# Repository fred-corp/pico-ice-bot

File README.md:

# Pico ICE Bot

A simple robot chassis bot for the Pico-ICE FPGA dev board.

## License & Acknowledgements

Made with ❤️, lots of ☕️, and lack of 🛌  
Published under CreativeCommons BY-SA 4.0

This work is licensed under a [Creative Commons Attribution-ShareAlike 4.0 International License](http://creativecommons.org/licenses/by-sa/4.0/).

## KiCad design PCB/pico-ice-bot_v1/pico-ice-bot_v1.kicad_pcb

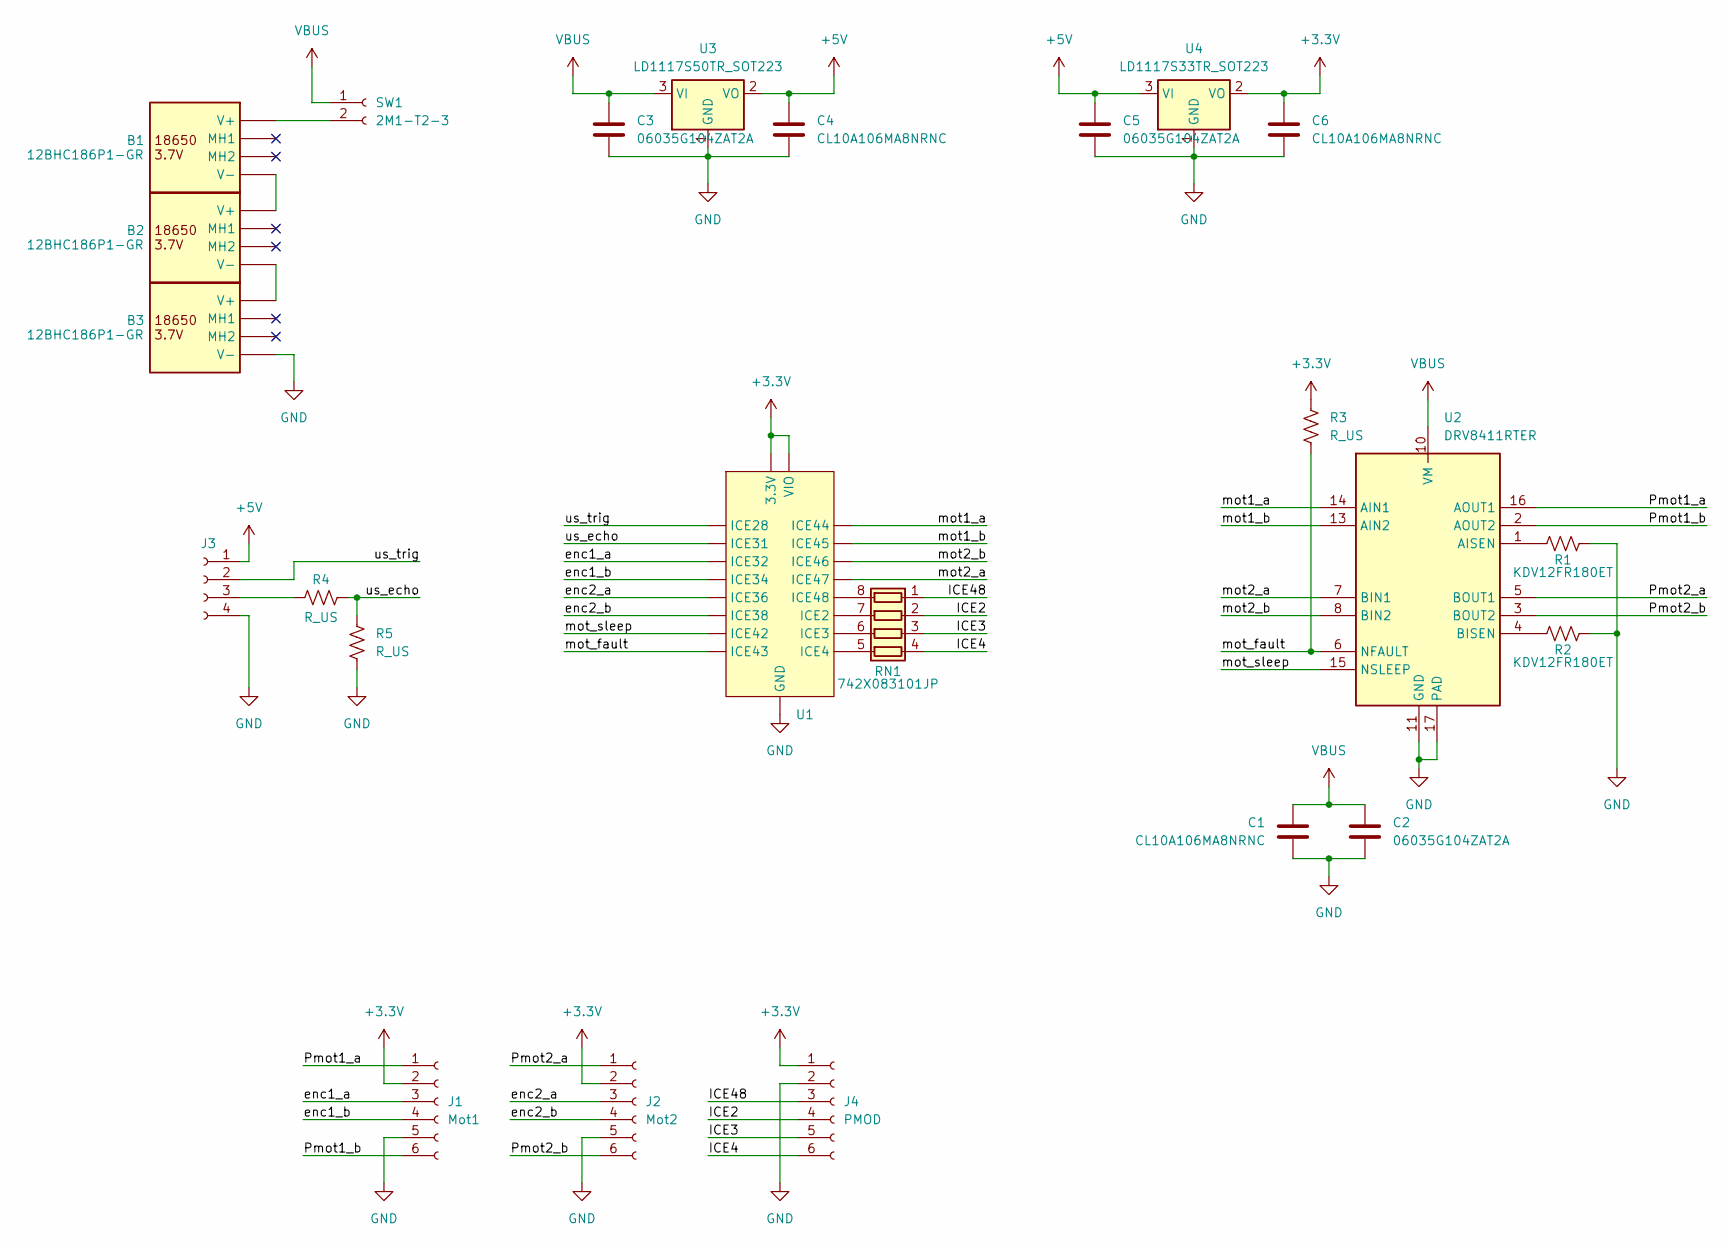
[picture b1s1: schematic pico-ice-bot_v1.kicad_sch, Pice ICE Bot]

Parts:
B1, B2, B3: 12BHC186P1-GR; 12BHC186P1GR; Mouser Part Number 12BHC186P1-GR
C1, C4, C6: CL10A106MA8NRNC; C_0603_1608Metric_Pad1.08x0.95mm_HandSolder
C2, C3, C5: 06035G104ZAT2A; C_0603_1608Metric_Pad1.08x0.95mm_HandSolder
J1: Mot1; PinSocket_1x06_P2.54mm_Vertical
J2: Mot2; PinSocket_1x06_P2.54mm_Vertical
J3: Conn_01x04_Socket; PinHeader_1x04_P2.54mm_Vertical
J4: PMOD; PinSocket_1x06_P2.54mm_Vertical
R1, R2: KDV12FR180ET; R_1206_3216Metric_Pad1.30x1.75mm_HandSolder
R3, R4, R5: R_US; R_0603_1608Metric_Pad0.98x0.95mm_HandSolder
RN1: 742X083101JP; R_Array_Concave_4x0603
SW1: 2M1-T2-3; PinHeader_1x02_P2.54mm_Vertical
U1: pico-ice-pmod_vertical
U2: DRV8411RTER; QFN50P300X300X80-17N-D; Mouser Part Number 595-DRV8411RTER
U3: LD1117S50TR_SOT223; SOT-223-3_TabPin2
U4: LD1117S33TR_SOT223; SOT-223-3_TabPin2

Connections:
+3.3V: C6.1, J1.2, J2.2, J4.1, R3.1, U1.1 (3.3V), U1.2 (3.3V), U1.13 (VIO), U1.14 (VIO), U4.2 (VO)
+5V: C4.1, C5.1, J3.1, U3.2 (VO), U4.3 (VI)
/ICE2: J4.4, RN1.2 (R2.1)
/ICE3: J4.5, RN1.3 (R3.1)
/ICE4: J4.6, RN1.4 (R4.1)
/ICE48: J4.3, RN1.1 (R1.1)
/Pmot1_a: J1.1, U2.16 (AOUT1)
/Pmot1_b: J1.6, U2.2 (AOUT2)
/Pmot2_a: J2.1, U2.5 (BOUT1)
/Pmot2_b: J2.6, U2.3 (BOUT2)
/enc1_a: J1.3, U1.7 (ICE32)
/enc1_b: J1.4, U1.8 (ICE34)
/enc2_a: J2.3, U1.9 (ICE36)
/enc2_b: J2.4, U1.10 (ICE38)
/mot1_a: U1.17 (ICE44), U2.14 (AIN1)
/mot1_b: U1.18 (ICE45), U2.13 (AIN2)
/mot2_a: U1.20 (ICE47), U2.7 (BIN1)
/mot2_b: U1.19 (ICE46), U2.8 (BIN2)
/mot_fault: R3.2, U1.12 (ICE43), U2.6 (NFAULT)
/mot_sleep: U1.11 (ICE42), U2.15 (NSLEEP)
/us_echo: R4.2, R5.1, U1.6 (ICE31)
/us_trig: J3.2, U1.5 (ICE28)
GND: B3.2 (V-), C1.2, C2.2, C3.2, C4.2, C5.2, C6.2, J1.5, J2.5, J3.4, J4.2, R1.2, R2.2, R5.2, U1.3 (GND), U1.4 (GND), U1.15 (GND), U1.16 (GND), U2.11 (GND), U2.17 (PAD), U3.1 (GND), U4.1 (GND)
unnamed: B1.1 (V+), SW1.2
unnamed: B1.2 (V-), B2.1 (V+)
unnamed: B2.2 (V-), B3.1 (V+)
unnamed: J3.3, R4.1
unnamed: RN1.8 (R1.2), U1.21 (ICE48)
unnamed: RN1.7 (R2.2), U1.22 (ICE2)
unnamed: RN1.6 (R3.2), U1.23 (ICE3)
unnamed: RN1.5 (R4.2), U1.24 (ICE4)
unnamed: R1.1, U2.1 (AISEN)
unnamed: R2.1, U2.4 (BISEN)
VBUS: C1.1, C2.1, C3.1, SW1.1, U2.10 (VM), U3.3 (VI)

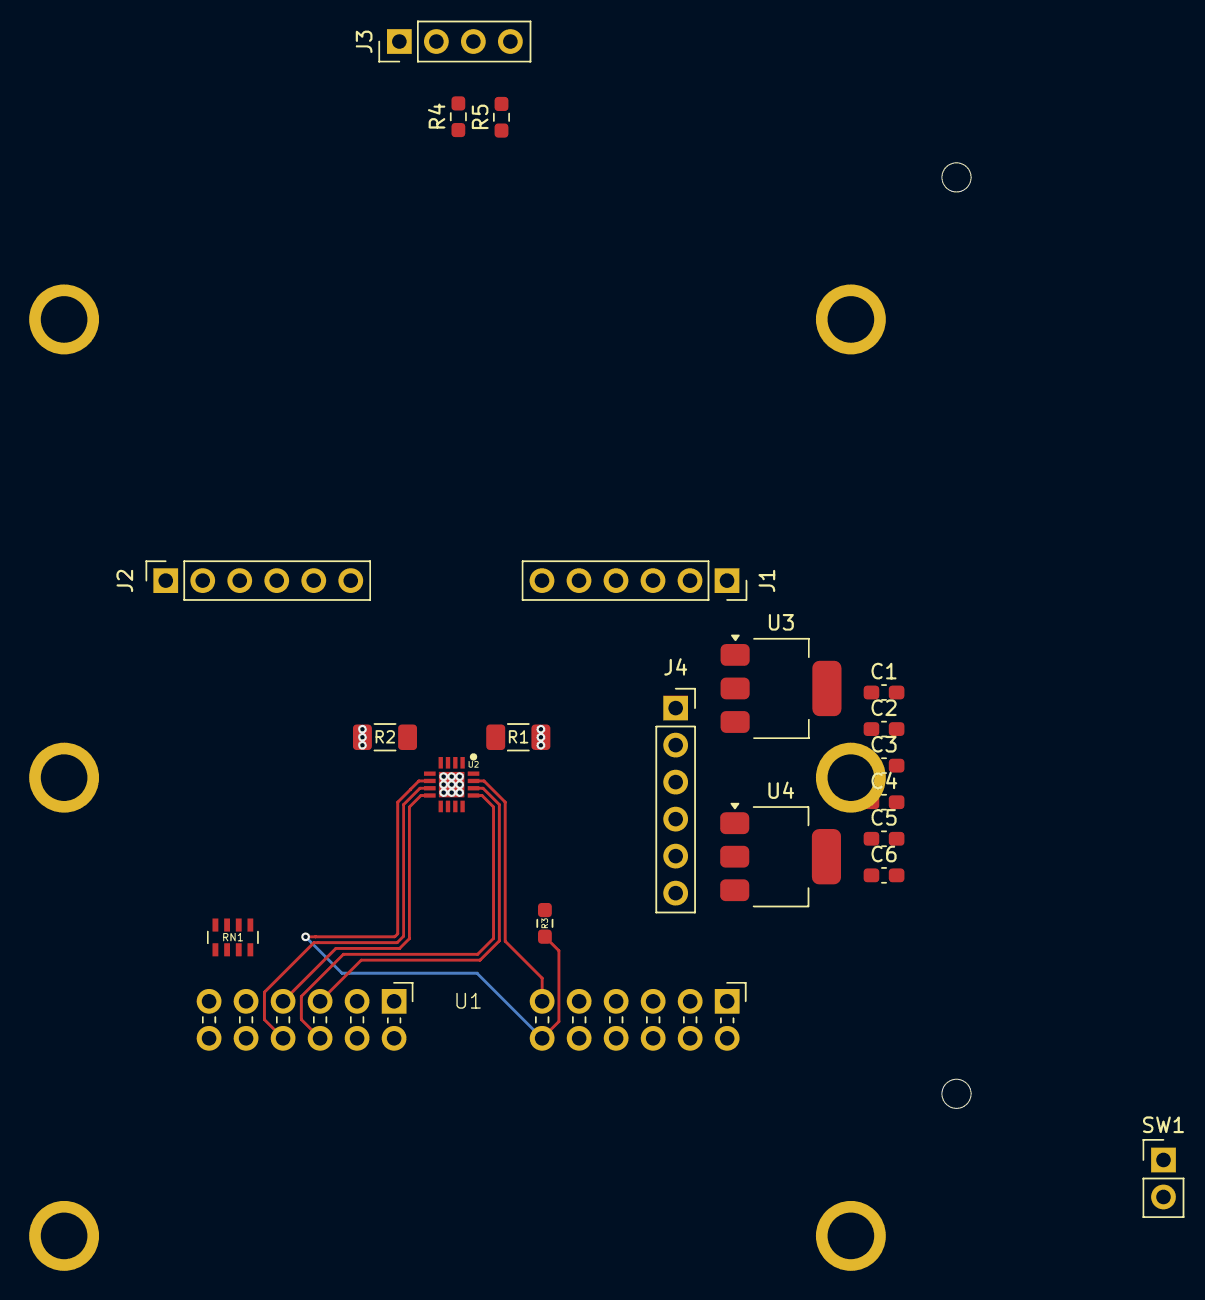
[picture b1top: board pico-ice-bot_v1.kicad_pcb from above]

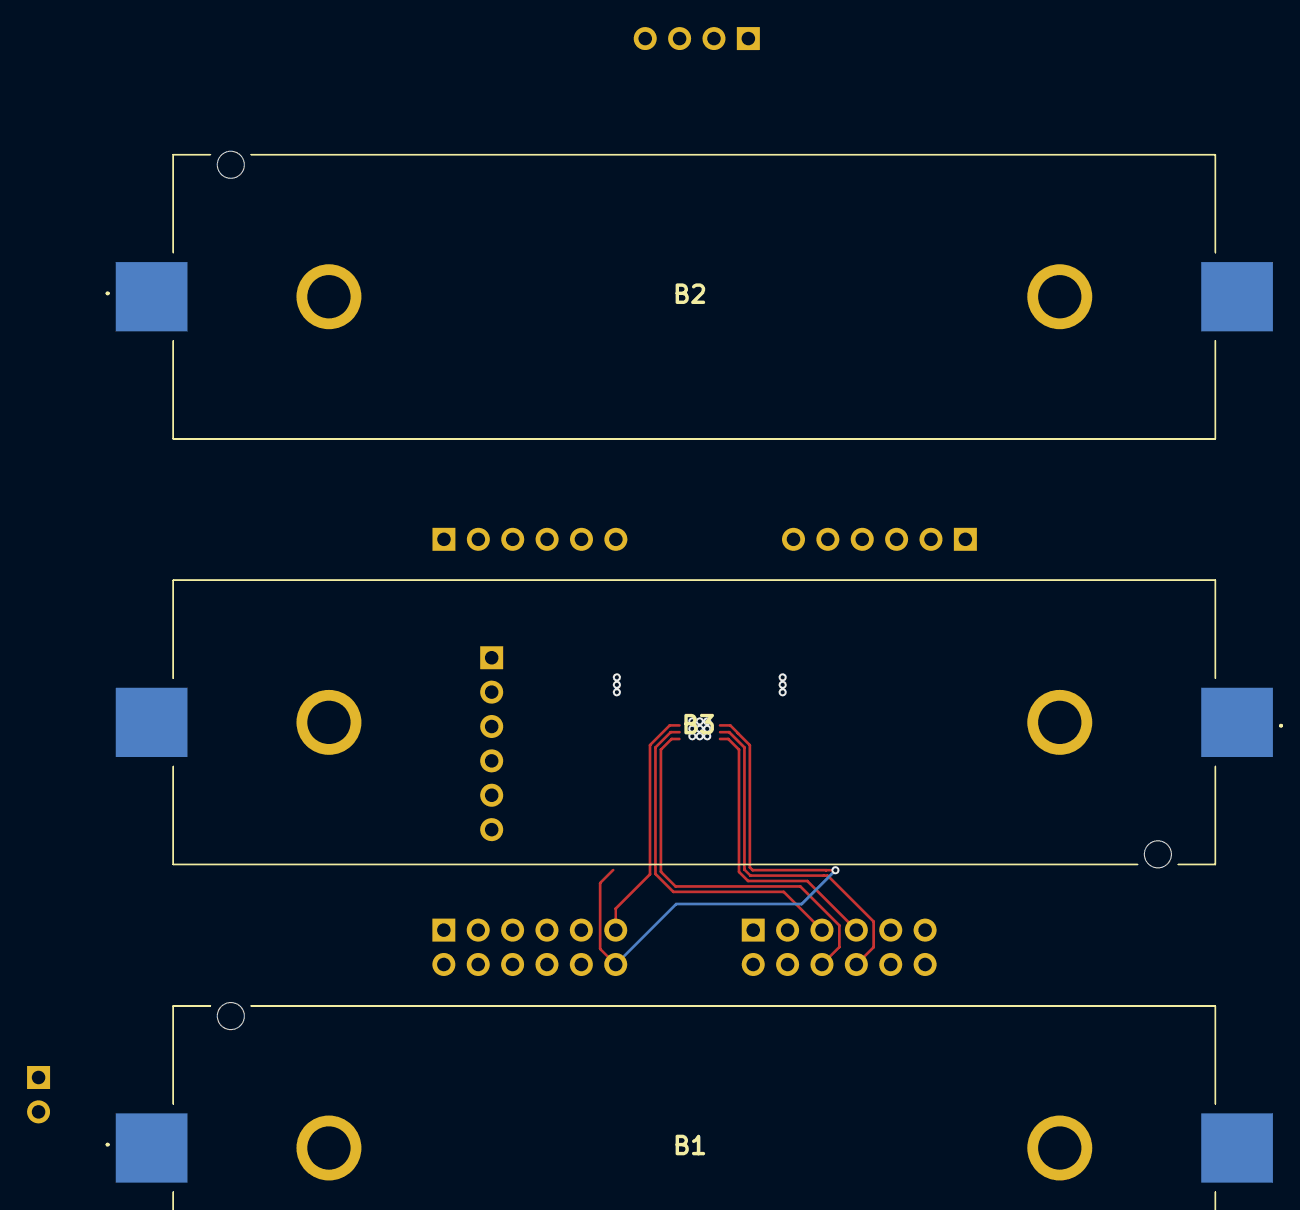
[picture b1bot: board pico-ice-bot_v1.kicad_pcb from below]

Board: 2 copper layers, 24 parts (3 on the bottom side), 34 nets.

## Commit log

2025-04-14 added trinity of git repo files
2025-04-14 added first draft & pcb project files for robot motherboard
2025-04-16 updated some files
2025-04-23 updated schematic and PCB Added batteries, power regulation
2025-04-23 update title block and adjust component positions in PCB and schematic files
